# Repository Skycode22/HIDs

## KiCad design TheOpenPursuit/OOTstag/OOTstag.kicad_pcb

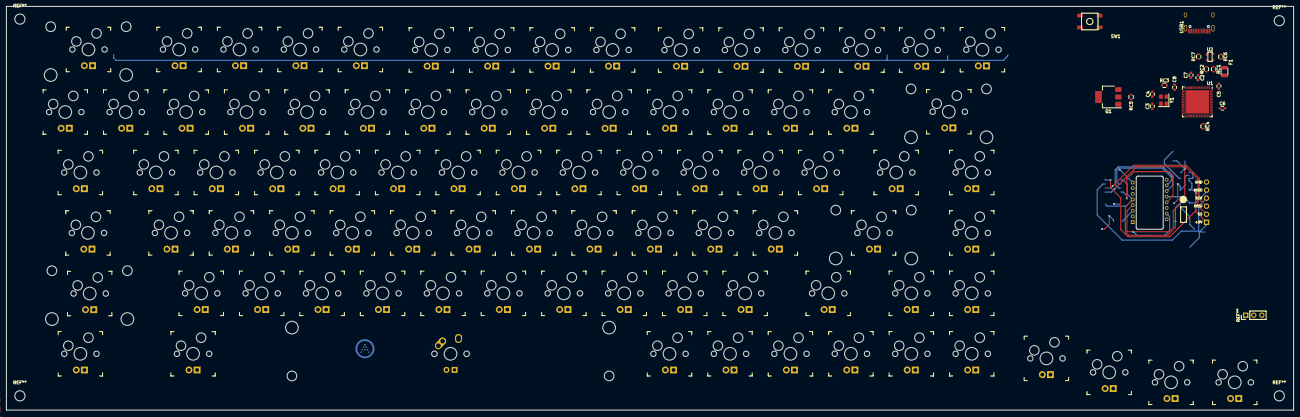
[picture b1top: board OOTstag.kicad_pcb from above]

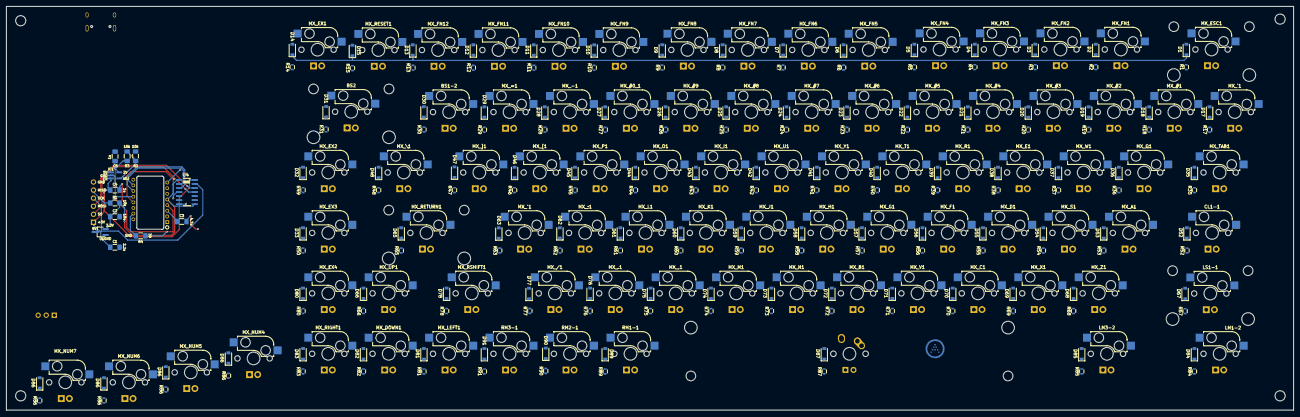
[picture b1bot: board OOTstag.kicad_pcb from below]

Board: 2 copper layers, 405.8 x 127.2 mm, 293 parts (185 on the bottom side), 14 nets.

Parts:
BS1-2: Kailh_socket_MX_led
BS2: Kailh_socket_MX_led stab
C1: 2.2uF; C_1206_3216Metric_Pad1.42x1.75mm_HandSolder
C2, C5: 1uF; C_0603
C2#2: 10uF; C_1206_3216Metric_Pad1.42x1.75mm_HandSolder
C3, C4: 22pF; C_0603
C3#2: 4.7uF; C_1206_3216Metric_Pad1.42x1.75mm_HandSolder
C4#2, C5#2: 1uF; C_1206_3216Metric_Pad1.42x1.75mm_HandSolder
C6, C7, C8: 0.1uF; C_0603
CL1-1: Kailh_socket_MX_led
D1, D2, D3, D4, D5, D6, D7, D8, D9, D10, D11, D12, D13, D14, D15, D17, D18, D19, D20, D21, D22, D23, D24, D25, D26, D27, D28, D29, D30, D31, D32, D33, D35, D36, D37, D38, D39, D40, D41, D42, D43, D44, D45, D46, D47, D48, D52, D53, D54, D55, D56, D57, D58, D59, D60, D61, D62, D63, D65, D66, D67, D68, D69, D70, D71, D72, D73, D74, D75, D76, D77, D78, D80, D81, D82, D83, D84, D85, D86, D86#2, D86#3, D86#4, D87, D89, D90, D91: SOD-323; D_SOD-123
F1: 500mA; Fuse_SMD1206_Reflow
IC1: AP7335-WG-7; AP7331
J1: Conn_01x06_Female; PinHeader_1x06_P2.54mm_Vertical
LM1-2: MX-1.5U; Kailh_socket_MX_led
LM3-2: Kailh_socket_MX_led
LS1-1: Kailh_socket_MX_led stab
MX_#0_1, MX_#1, MX_#2, MX_#3, MX_#4, MX_#5, MX_#6, MX_#7, MX_#8, MX_#9: Kailh_socket_MX_led
MX_'1: Kailh_socket_MX_led
MX_,1: Kailh_socket_MX_led
MX_-1: Kailh_socket_MX_led
MX_.1: Kailh_socket_MX_led
MX_/1: Kailh_socket_MX_led
MX_;1: Kailh_socket_MX_led
MX_=1: Kailh_socket_MX_led
MX_A1: Kailh_socket_MX_led
MX_B1: Kailh_socket_MX_led
MX_C1: Kailh_socket_MX_led
MX_D1: Kailh_socket_MX_led
MX_DOWN1: Kailh_socket_MX_led
MX_E1: Kailh_socket_MX_led
MX_ESC1: Kailh_socket_MX_led stab
MX_EX1, MX_EX2, MX_EX3, MX_EX4: Kailh_socket_MX_led
MX_F1: Kailh_socket_MX_led
MX_FN1, MX_FN2, MX_FN3, MX_FN4, MX_FN5, MX_FN6, MX_FN7, MX_FN8, MX_FN9, MX_FN10, MX_FN11, MX_FN12: Kailh_socket_MX_led
MX_G1: Kailh_socket_MX_led
MX_H1: Kailh_socket_MX_led
MX_I1: Kailh_socket_MX_led
MX_J1: Kailh_socket_MX_led
MX_K1: Kailh_socket_MX_led
MX_L1: Kailh_socket_MX_led
MX_LEFT1: Kailh_socket_MX_led
MX_M1: Kailh_socket_MX_led
MX_N1: Kailh_socket_MX_led
MX_NUM4, MX_NUM5, MX_NUM6, MX_NUM7: Kailh_socket_MX_led
MX_O1: Kailh_socket_MX_led
MX_P1: Kailh_socket_MX_led
MX_Q1: Kailh_socket_MX_led
MX_R1: Kailh_socket_MX_led
MX_RESET1: Kailh_socket_MX_led
MX_RETURN1: Kailh_socket_MX_led stab
MX_RIGHT1: Kailh_socket_MX_led
MX_RSHIFT1: Kailh_socket_MX_led
MX_S1: Kailh_socket_MX_led
MX_T1: Kailh_socket_MX_led
MX_TAB1: Kailh_socket_MX_led
MX_U1: Kailh_socket_MX_led
MX_UP1: Kailh_socket_MX_led
MX_V1: Kailh_socket_MX_led
MX_W1: Kailh_socket_MX_led
MX_X1: Kailh_socket_MX_led
MX_Y1: Kailh_socket_MX_led
MX_Z1: Kailh_socket_MX_led
MX_[1: Kailh_socket_MX_led
MX_\1: Kailh_socket_MX_led
MX_]1: Kailh_socket_MX_led
MX_`1: Kailh_socket_MX_led
Q1: DSS60601MZ4-13; SOT-223-3_TabPin2
R1, R2#2: 10k; R_1206_3216Metric_Pad1.42x1.75mm_HandSolder
R1#2, R2, R3, R4, R5, R6, R7, R8, R9, R10, R11, R12, R13, R14, R15, R17, R18, R19, R20, R21, R22, R23, R24, R25, R26, R27, R28, R29, R30, R31, R35, R36, R37, R38, R39, R40, R41, R42, R43, R44, R45, R46, R47, R48, R49, R50, R52, R53, R54, R55, R56, R57, R58, R59, R60, R61, R62, R63, R65, R66, R67, R68, R69, R70, R71, R72, R73, R74, R75, R76, R77, R78, R80, R81, R82, R83, R84, R85, R86, R86#2, R86#3, R86#4, R87, R89, R90, R91: 1k; R_0603
R3#2: 15k; R_1206_3216Metric_Pad1.42x1.75mm_HandSolder
R4#2: 39; R_1206_3216Metric_Pad1.42x1.75mm_HandSolder
RC1, RC2: 22; R_0603
RC3: 10k; R_0603
RC4: 1k; R_0603
RC5: 1.5k; R_0603
RC6, RC7: 5k1; R_0603
RM1-1, RM2-1, RM3-1: Kailh_socket_MX_led
SP1: MX-6.25U; MX-6.25U-ReversedStabilizers
SW1: SW_Push; SKQG-1155865
U1: AT90USB1286-AU; QFN-64-1EP_9x9mm_Pitch0.5mm
U1#2: XC6206P332MR; TSOT-23_HandSoldering
U2: PRTR5V0U2X; SOT143B
U2#2: PMW3360DM-T2QU; DIP-16_W10.16mm
U4: TXS0104EDR; SOIC127P600X175-14N
USB1: HRO-TYPE-C-31-M-12; HRO-TYPE-C-31-M-12-Assembly
Y1: 16MHz; Crystal_SMD_3225-4pin_3.2x2.5mm

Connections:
GND: C1.2, C2#2.2, C3#2.2, C4#2.2, C5#2.2, IC1.2 (GND), J1.1, R2#2.2, U1#2.1 (GND), U2#2.8 (GND), U4.7 (GND)
MISO: J1.2, R1.2, U2#2.12 (MISO)
MOSI: U2#2.11 (MOSI), U4.3 (A2)
MOSI_I: J1.4, U4.12 (B2)
NCS: U2#2.13 (NCS), U4.4 (A3)
NCS_I: J1.5, U4.11 (B3)
unnamed: C3#2.1, U2#2.3 (VDDPIX)
unnamed: IC1.4 (ADJ), R2#2.1, R3#2.1
unnamed: R4#2.2, U2#2.15 (LED_P)
SCLK: U2#2.10 (SCLK), U4.2 (A1)
SCLK_I: J1.3, U4.13 (B1)
VDD_2V: C5#2.1, IC1.5 (OUT), R3#2.2, R4#2.1, U2#2.4 (VDD)
VDD_3.3V: C2#2.1, R1.1, U1#2.2 (VO), U2#2.5 (VDDIO), U4.1 (VCCA), U4.8 (OE)
VDD_5V: C1.1, C4#2.1, IC1.1 (IN), IC1.3 (EN), J1.6, U1#2.3 (VI), U4.14 (VCCB)

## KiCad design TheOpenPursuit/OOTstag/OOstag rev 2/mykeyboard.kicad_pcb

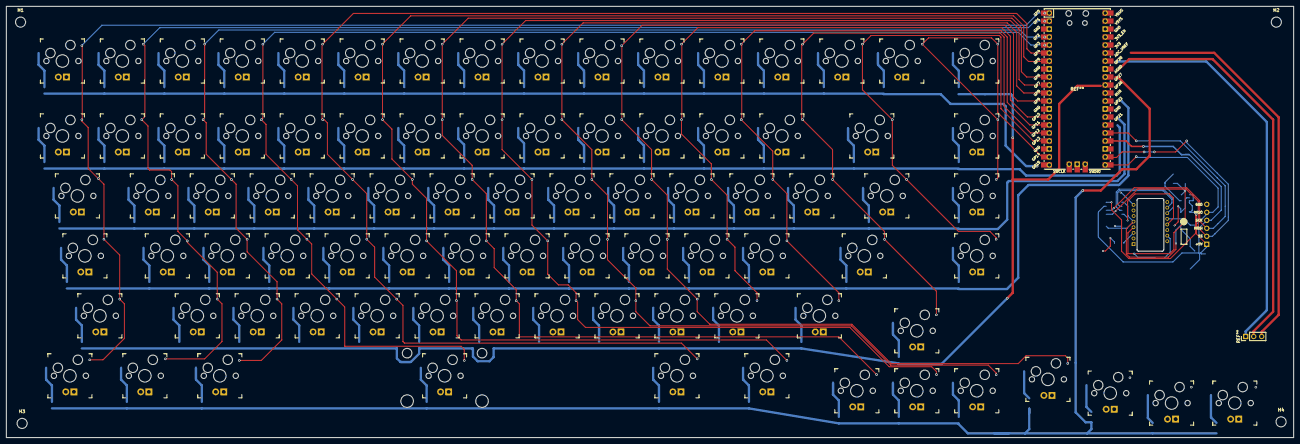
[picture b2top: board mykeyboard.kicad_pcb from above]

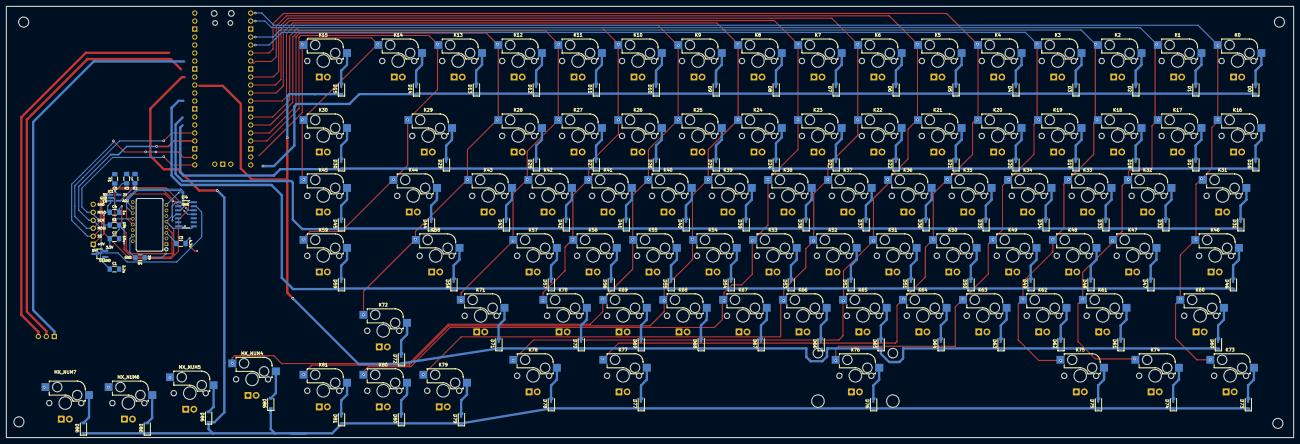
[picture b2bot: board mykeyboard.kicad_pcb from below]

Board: 2 copper layers, 409.0 x 137.0 mm, 190 parts (99 on the bottom side), 105 nets.

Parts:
C1: 2.2uF; C_1206_3216Metric_Pad1.42x1.75mm_HandSolder
C2: 10uF; C_1206_3216Metric_Pad1.42x1.75mm_HandSolder
C3: 4.7uF; C_1206_3216Metric_Pad1.42x1.75mm_HandSolder
C4, C5: 1uF; C_1206_3216Metric_Pad1.42x1.75mm_HandSolder
D0, D1, D2, D3, D4, D5, D6, D7, D8, D9, D10, D11, D12, D13, D14, D15, D16, D17, D18, D19, D20, D21, D22, D23, D24, D25, D26, D27, D28, D29, D30, D31, D32, D33, D34, D35, D36, D37, D38, D39, D40, D41, D42, D43, D44, D45, D46, D47, D48, D49, D50, D51, D52, D53, D54, D55, D56, D57, D58, D59, D60, D61, D62, D63, D64, D65, D66, D67, D68, D69, D70, D71, D72, D73, D74, D75, D76, D77, D78, D79, D80, D81: D; D_SOD-123
D86, D86#2, D86#3, D86#4: SOD-323; D_SOD-123
H1, H2, H3, H4: MountingHole; MountingHole_3.2mm_M3_DIN965
IC1: AP7335-WG-7; AP7331
J1: Conn_01x06_Female; PinHeader_1x06_P2.54mm_Vertical
K0: Esc; Kailh_socket_MX_led
K1: F1; Kailh_socket_MX_led
K2: F2; Kailh_socket_MX_led
K3: F3; Kailh_socket_MX_led
K4: F4; Kailh_socket_MX_led
K5: F5; Kailh_socket_MX_led
K6: F6; Kailh_socket_MX_led
K7: F7; Kailh_socket_MX_led
K8: F8; Kailh_socket_MX_led
K9: F9; Kailh_socket_MX_led
K10: F10; Kailh_socket_MX_led
K11: F11; Kailh_socket_MX_led
K12: F12; Kailh_socket_MX_led
K13: Home; Kailh_socket_MX_led
K14: End; Kailh_socket_MX_led
K15: Insert; Kailh_socket_MX_led
K16: ~,`; Kailh_socket_MX_led
K17: !,1; Kailh_socket_MX_led
K18: @,2; Kailh_socket_MX_led
K19: #,3; Kailh_socket_MX_led
K20: $,4; Kailh_socket_MX_led
K21: %,5; Kailh_socket_MX_led
K22: ^,6; Kailh_socket_MX_led
K23: &,7; Kailh_socket_MX_led
K24: *,8; Kailh_socket_MX_led
K25: (,9; Kailh_socket_MX_led
K26: ),0; Kailh_socket_MX_led
K27: _,-; Kailh_socket_MX_led
K28: +,=; Kailh_socket_MX_led
K29: Backspace; Kailh_socket_MX_led
K30: Delete; Kailh_socket_MX_led
K31: Tab; Kailh_socket_MX_led
K32: Q; Kailh_socket_MX_led
K33: W; Kailh_socket_MX_led
K34: E; Kailh_socket_MX_led
K35: R; Kailh_socket_MX_led
K36: T; Kailh_socket_MX_led
K37: Y; Kailh_socket_MX_led
K38: U; Kailh_socket_MX_led
K39: I; Kailh_socket_MX_led
K40: O; Kailh_socket_MX_led
K41: P; Kailh_socket_MX_led
K42: {,[; Kailh_socket_MX_led
K43: },]; Kailh_socket_MX_led
K44: |,\; Kailh_socket_MX_led
K45: PgUp; Kailh_socket_MX_led
K46: Caps Lock; Kailh_socket_MX_led
K47: A; Kailh_socket_MX_led
K48: S; Kailh_socket_MX_led
K49: D; Kailh_socket_MX_led
K50: F; Kailh_socket_MX_led
K51: G; Kailh_socket_MX_led
K52: H; Kailh_socket_MX_led
K53: J; Kailh_socket_MX_led
K54: K; Kailh_socket_MX_led
K55: L; Kailh_socket_MX_led
K56: :,;; Kailh_socket_MX_led
K57: ",'; Kailh_socket_MX_led
K58: Enter; Kailh_socket_MX_led
K59: PgDn; Kailh_socket_MX_led
K60, K71: Shift; Kailh_socket_MX_led
K61: Z; Kailh_socket_MX_led
K62: X; Kailh_socket_MX_led
K63: C; Kailh_socket_MX_led
K64: V; Kailh_socket_MX_led
K65: B; Kailh_socket_MX_led
K66: N; Kailh_socket_MX_led
K67: M; Kailh_socket_MX_led
K68: <,,; Kailh_socket_MX_led
K69: >,.; Kailh_socket_MX_led
K70: ?,/; Kailh_socket_MX_led
K72: ↑; Kailh_socket_MX_led
K73, K78: Ctrl; Kailh_socket_MX_led
K74: Win; Kailh_socket_MX_led
K75, K77: Alt; Kailh_socket_MX_led
K76: Space; Kailh_socket_MX_led stab
K79: ←; Kailh_socket_MX_led
K80: ↓; Kailh_socket_MX_led
K81: →; Kailh_socket_MX_led
MX_NUM4, MX_NUM5, MX_NUM6, MX_NUM7: Kailh_socket_MX_led
R1, R2: 10k; R_1206_3216Metric_Pad1.42x1.75mm_HandSolder
R3: 15k; R_1206_3216Metric_Pad1.42x1.75mm_HandSolder
R4: 39; R_1206_3216Metric_Pad1.42x1.75mm_HandSolder
U1: XC6206P332MR; TSOT-23_HandSoldering
U2: PMW3360DM-T2QU; DIP-16_W10.16mm
U4: TXS0104EDR; SOIC127P600X175-14N

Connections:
/Col_0: K0.1, K16.1, K31.1, K46.1, K60.1, K73.1
/Col_1: K1.1, K17.1, K32.1, K47.1, K61.1, K74.1
/Col_2: K2.1, K18.1, K33.1, K48.1, K62.1, K75.1
/Col_3: K3.1, K19.1, K34.1, K49.1, K63.1, K76.1
/Col_4: K4.1, K20.1, K35.1, K50.1, K64.1, K77.1
/Col_5: K5.1, K21.1, K36.1, K51.1, K65.1, K78.1
/Col_6: K6.1, K22.1, K37.1, K52.1, K66.1, K79.1
/Col_7: K7.1, K23.1, K38.1, K53.1, K67.1, K80.1
/Col_8: K8.1, K24.1, K39.1, K54.1, K68.1, K81.1
/Col_9: K9.1, K25.1, K40.1, K55.1, K69.1, MX_NUM4.1
/Col_10: K10.1, K26.1, K41.1, K56.1, K70.1, MX_NUM5.1
/Col_11: K11.1, K27.1, K42.1, K57.1, K71.1, MX_NUM6.1
/Col_12: K12.1, K28.1, K43.1, K58.1, K72.1, MX_NUM7.1
/Col_13: K13.1, K29.1, K44.1, K59.1
/Col_14: K14.1, K15.1, K30.1, K45.1
/Row_0: D0.1, D1.1, D2.1, D3.1, D4.1, D5.1, D6.1, D7.1, D8.1, D9.1, D10.1, D11.1, D12.1, D13.1, D14.1
/Row_1: D16.1, D17.1, D18.1, D19.1, D20.1, D21.1, D22.1, D23.1, D24.1, D25.1, D26.1, D27.1, D28.1, D29.1, D30.1
/Row_2: D31.1, D32.1, D33.1, D34.1, D35.1, D36.1, D37.1, D38.1, D39.1, D40.1, D41.1, D42.1, D43.1, D44.1, D45.1
/Row_3: D46.1, D47.1, D48.1, D49.1, D50.1, D51.1, D52.1, D53.1, D54.1, D55.1, D56.1, D57.1, D58.1, D59.1
/Row_4: D15.1, D60.1, D61.1, D62.1, D63.1, D64.1, D65.1, D66.1, D67.1, D68.1, D69.1, D70.1, D71.1, D72.1
/Row_5: D73.1, D74.1, D75.1, D76.1, D77.1, D78.1, D79.1, D80.1, D81.1, D86.1, D86#2.1, D86#3.1, D86#4.1
GND: C1.2, C2.2, C3.2, C4.2, C5.2, IC1.2 (GND), J1.1, R2.2, U1.1 (GND), U2.8 (GND), U4.7 (GND)
unnamed: D0.2, K0.2
unnamed: D1.2, K1.2
unnamed: D2.2, K2.2
unnamed: D3.2, K3.2
unnamed: D4.2, K4.2
unnamed: D5.2, K5.2
unnamed: D6.2, K6.2
unnamed: D7.2, K7.2
unnamed: D8.2, K8.2
unnamed: D9.2, K9.2
unnamed: D10.2, K10.2
unnamed: D11.2, K11.2
unnamed: D12.2, K12.2
unnamed: D13.2, K13.2
unnamed: D14.2, K14.2
unnamed: D15.2, K15.2
unnamed: D16.2, K16.2
unnamed: D17.2, K17.2
unnamed: D18.2, K18.2
unnamed: D19.2, K19.2
unnamed: D20.2, K20.2
unnamed: D21.2, K21.2
unnamed: D22.2, K22.2
unnamed: D23.2, K23.2
unnamed: D24.2, K24.2
unnamed: D25.2, K25.2
unnamed: D26.2, K26.2
unnamed: D27.2, K27.2
unnamed: D28.2, K28.2
unnamed: D29.2, K29.2
unnamed: D30.2, K30.2
unnamed: D31.2, K31.2
unnamed: D32.2, K32.2
unnamed: D33.2, K33.2
unnamed: D34.2, K34.2
unnamed: D35.2, K35.2
unnamed: D36.2, K36.2
unnamed: D37.2, K37.2
unnamed: D38.2, K38.2
unnamed: D39.2, K39.2
unnamed: D40.2, K40.2
unnamed: D41.2, K41.2
unnamed: D42.2, K42.2
unnamed: D43.2, K43.2
unnamed: D44.2, K44.2
unnamed: D45.2, K45.2
unnamed: D46.2, K46.2
unnamed: D47.2, K47.2
unnamed: D48.2, K48.2
unnamed: D49.2, K49.2
unnamed: D50.2, K50.2
unnamed: D51.2, K51.2
unnamed: D52.2, K52.2
unnamed: D53.2, K53.2
unnamed: D54.2, K54.2
unnamed: D55.2, K55.2
unnamed: D56.2, K56.2
unnamed: D57.2, K57.2
unnamed: D58.2, K58.2
unnamed: D59.2, K59.2
unnamed: D60.2, K60.2
unnamed: D61.2, K61.2
unnamed: D62.2, K62.2
unnamed: D63.2, K63.2
unnamed: D64.2, K64.2
unnamed: D65.2, K65.2
unnamed: D66.2, K66.2
unnamed: D67.2, K67.2
unnamed: D68.2, K68.2
unnamed: D69.2, K69.2
unnamed: D70.2, K70.2
unnamed: D71.2, K71.2
unnamed: D72.2, K72.2
unnamed: D73.2, K73.2
unnamed: D74.2, K74.2
unnamed: D75.2, K75.2
unnamed: D76.2, K76.2
unnamed: D77.2, K77.2
unnamed: D78.2, K78.2
unnamed: D79.2, K79.2
unnamed: D80.2, K80.2
unnamed: D81.2, K81.2
unnamed: R4.2, U2.15 (LED_P)
